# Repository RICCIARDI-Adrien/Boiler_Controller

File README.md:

# Boiler Controller

## Hardware
Schematics have been drawn using Eagle 8.3.1.  

### Power board
This board contains the AC/DC converter, the relays and the connector to the wall housing.

### Controller board
This board holds the microcontroller and the WiFi to UART bridge.

### Components
* [Single pole 16A relay with 5V coil](http://fr.farnell.com/oeg-te-connectivity/omih-ss-105lm-300/relais-spst-no-250vac-30vdc-16a/dp/1891727)
* [BD135 NPN bipolar transistor](http://fr.farnell.com/stmicroelectronics/bd135/transistor-npn-to-126/dp/9801529)
* [1N4007 rectifier diode](http://fr.farnell.com/multicomp/1n4007/diode-1a-1000v/dp/9565051)
* [15pF ceramic capacitor](http://fr.farnell.com/multicomp/mc0805n150j101a2-54mm/condensateur-mlcc-c0g-np0-15pf/dp/2112750)
* [100nF ceramic capacitor](http://fr.farnell.com/multicomp/mc0805b104k500a5-08mm/condensateur-mlcc-0-1uf-50v-x7r/dp/2395773)
* [10uF electrolytic capacitor](http://fr.farnell.com/multicomp/mcgpr16v106m5x11/condensateur-elec-alu-10uf-16v/dp/9451056)
* [10uF tantalum capacitor](http://fr.farnell.com/multicomp/mctar16v106kc/condensateur-tantale-10uf-16v/dp/2395815)
* [5V 2A AC/DC power supply](http://fr.farnell.com/vigortronix/vtx-214-010-205/alimentation-ac-dc-5v-2a/dp/2464685)
* [160ohm 1% resistor](http://fr.farnell.com/multicomp/mf12-160r/resistance-0-125w-1-160r/dp/9342672)
* [330ohm 5% resistor](http://fr.farnell.com/multicomp/mcf-0-25w-330r/resistance-couche-carbon-330r/dp/9339418)
* [470ohm 1% resistor](http://fr.farnell.com/multicomp/mf50-470r/resistance-0-5w-1-470r/dp/9340610)
* [1Kohm 5% resistor](http://fr.farnell.com/multicomp/mcf-0-25w-1k/resistance-couche-carbon-1k-0/dp/9339051)
* [1Kohm 1% resistor](http://fr.farnell.com/multicomp/mf50-1k/resistance-1k-0-5w-1/dp/9339779)
* [Fuseholder](http://fr.farnell.com/littelfuse/64900001039/porte-fusible-cms-20x5mm/dp/1271673)
* [Fuse](http://fr.farnell.com/littelfuse/0232002-mxp/fuse-cartridge-medium-acting-2a/dp/1707348)
* [2-pad terminal](http://fr.farnell.com/camdenboss/ctb0708-2/bornier-standard-2-voies-30-12awg/dp/2315273)
* [4-pad terminal](http://fr.farnell.com/camdenboss/ctb0708-4/bornier-standard-4-voies-30-12awg/dp/2315275)
* [Atmega328p microcontroller](http://fr.farnell.com/microchip/atmega328p-pu/micro-8-bits-avr-32k-flash-28pdip/dp/1715487)
* [3.6864MHz crystal](http://fr.farnell.com/iqd-frequency-products/lfxtal003263/quartz-3-686400mhz/dp/9712909)
* [3.3V LDO](http://fr.farnell.com/texas-instruments/lm1086ct-3-3-nopb/ic-reg-ldo-3-3v-1-5a-to-220/dp/1564628)
* [WiFi to UART bridge](https://www.gotronic.fr/art-module-wifi-uart-grove-113020010-23827.htm)
* [4-pin PCB male connector](https://www.gotronic.fr/art-connecteur-s004-5858.htm)
* [4-pin PCB female connector](https://www.gotronic.fr/art-connecteur-p004-5867.htm)
* [10-pin PCB male connector](https://www.gotronic.fr/art-connecteur-s010-15367.htm)
* [10-pin PCB female connector](https://www.gotronic.fr/art-connecteur-p010-15370.htm)

### Analog signals characteristics
* Day trimmer : resistance variation from 50 to 110ohm.
* Night trimmer : resistance variation from 0 to 60ohm.
* Radiator water start thermistor : resistance variation from 580 (+80°C) to 900ohm (-20°C).
* Outside thermistor : resistance variation from 340 (+40°C) to 480ohm (-10°C).
  
Microcontroller uses a 3.3V precision voltage reference for the ADC module to gain more precision with small variation signals. All voltage dividers must be calculated as the highest variable resistance value results in a 3.3V maximum voltage on the ADC pin.

### Fuse value calculation
AC/DC converter inrush current is 40A for less than 500us, so a temporized fuse is needed to allow the board to boot.  
AC/DC converter maximum input current is 150mA @ 240V, but due to enormous inrush current a big fuse must be used. A 250V/2A fuse has been chosen because this is the fuse used on the VTX-214 demo board (http://www.farnell.com/datasheets/1878969.pdf).

## Software

### Building microcontroller firmware
Install `avr-gcc` to build the microcontroller firmware.
  
Go to `Software/Microcontroller_Firmware` directory and type the following command to build the firmware :
```
make
```
File `Boiler_Controller_Firmware.elf` will be created.

### Flashing microcontroller firmware
You need to install `avrdude` to access to the programmer.  
Firmware can be burnt to the microcontroller memory by connecting an AVR ISP programmer to the controller board ISP connector and typing the command :
```
make flash
```
  
You can override the `PROGRAMMER_SERIAL_PORT` environment variable with the serial port your programmer is connected to.

### Building web server
You need to install `libmicrohttpd` library before building.  
On Debian/Ubuntu system, use the command `sudo apt install libmicrohttpd-dev`.  

To build the web server, go to `Software/Web_Server` directory and type `make`.

### Installing web server
Go to `Software/Web_Server` directory, build web server then type `sudo make install` to install server and init script.  
You can use `sudo make uninstall` command to uninstall the server and all related files.

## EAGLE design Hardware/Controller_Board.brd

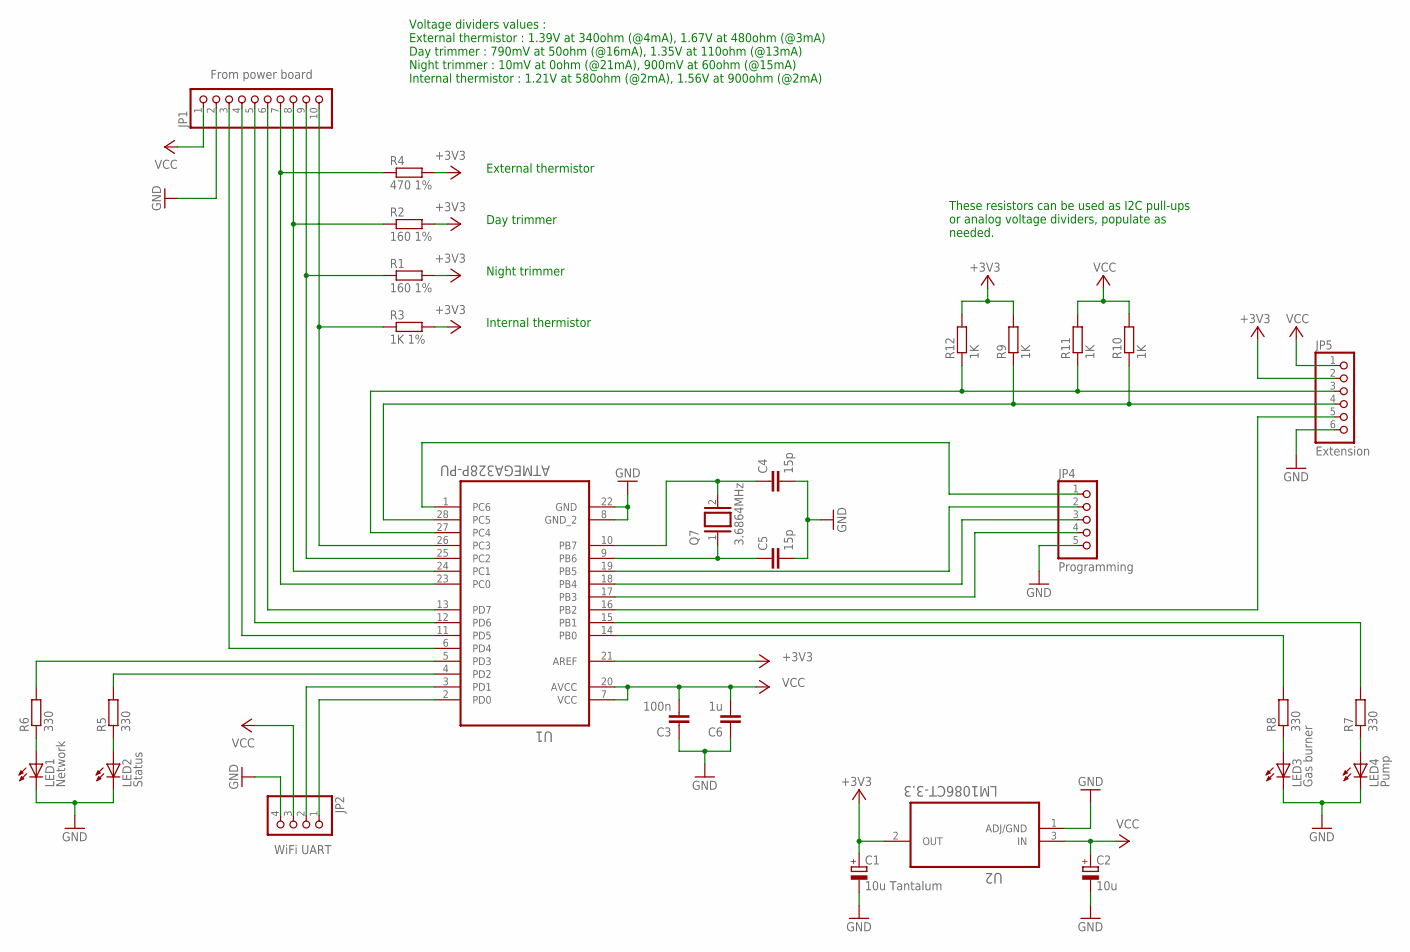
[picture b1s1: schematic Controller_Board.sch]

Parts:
C1: 10u Tantalum; E2,5-7
C2: 10u; E2,5-7
C3: 100n; C050-035X075
C4, C5: 15p; C025-050X050
C6: 1u; C050-035X075
JP1: From power board; 1X10
JP2: WiFi UART; 1X04
JP4: Programming; 1X05
JP5: Extension; 1X06
LED1: Network; LED5MM
LED2: Status; LED5MM
LED3: Gas burner; LED5MM
LED4: Pump; LED5MM
Q7: 3.6864MHz; QS
R1, R2: 160 1%; 0207/10
R3: 1K 1%; 0207/10
R4: 470 1%; 0207/10
R5, R6, R7, R8: 330; 0207/10
R9, R10, R11, R12: 1K; 0207/10
U1: ATMEGA328P-PU; DIP254P762X457-28
U2: LM1086CT-3.3; TO254P470X1016X2222-3P

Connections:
+3V3: C1.+, JP5.2, R1.2, R2.2, R3.2, R4.2, R9.2, R12.2, U1.21 (AREF), U2.2 (OUT)
GND: C1.-, C2.-, C3.1, C4.2, C5.2, C6.1, JP1.2, JP2.4, JP4.5, JP5.6, LED1.K (C), LED2.K (C), LED3.K (C), LED4.K (C), U1.8 (GND_2), U1.22 (GND), U2.1 (ADJ/GND)
unnamed: JP1.10, R3.1, U1.26 (PC3)
unnamed: JP1.9, R1.1, U1.25 (PC2)
unnamed: JP1.8, R2.1, U1.24 (PC1)
unnamed: JP1.7, R4.1, U1.23 (PC0)
unnamed: JP1.6, U1.13 (PD7)
unnamed: JP1.5, U1.12 (PD6)
unnamed: JP1.4, U1.11 (PD5)
unnamed: JP1.3, U1.6 (PD4)
unnamed: JP2.2, U1.3 (PD1)
unnamed: JP2.1, U1.2 (PD0)
unnamed: LED1.A, R6.1
unnamed: LED2.A, R5.1
unnamed: R6.2, U1.5 (PD3)
unnamed: R5.2, U1.4 (PD2)
unnamed: JP4.2, U1.19 (PB5)
unnamed: JP4.3, U1.18 (PB4)
unnamed: JP4.4, U1.17 (PB3)
unnamed: JP4.1, U1.1 (PC6)
unnamed: JP5.3, R11.1, R12.1, U1.27 (PC4)
unnamed: LED4.A, R7.1
unnamed: LED3.A, R8.1
unnamed: JP5.4, R9.1, R10.1, U1.28 (PC5)
unnamed: R8.2, U1.14 (PB0)
unnamed: R7.2, U1.15 (PB1)
unnamed: JP5.5, U1.16 (PB2)
unnamed: C4.1, Q7.2, U1.10 (PB7)
unnamed: C5.1, Q7.1, U1.9 (PB6)
VCC: C2.+, C3.2, C6.2, JP1.1, JP2.3, JP5.1, R10.2, R11.2, U1.7 (VCC), U1.20 (AVCC), U2.3 (IN)

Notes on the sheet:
Night trimmer
Day trimmer
Internal thermistor
External thermistor
Voltage dividers values : External thermistor : 1.39V at 340ohm (@4mA), 1.67V at 480ohm (@3mA) Day trimmer : 790mV at 50ohm (@16mA), 1.35V at 110ohm (@13mA) Night trimmer : 10mV at 0ohm (@21mA), 900mV at 60ohm (@15mA) Internal thermistor : 1.21V at 580ohm (@2mA), 1.56V at 900ohm (@2mA)
These resistors can be used as I2C pull-ups or analog voltage dividers, populate as needed.

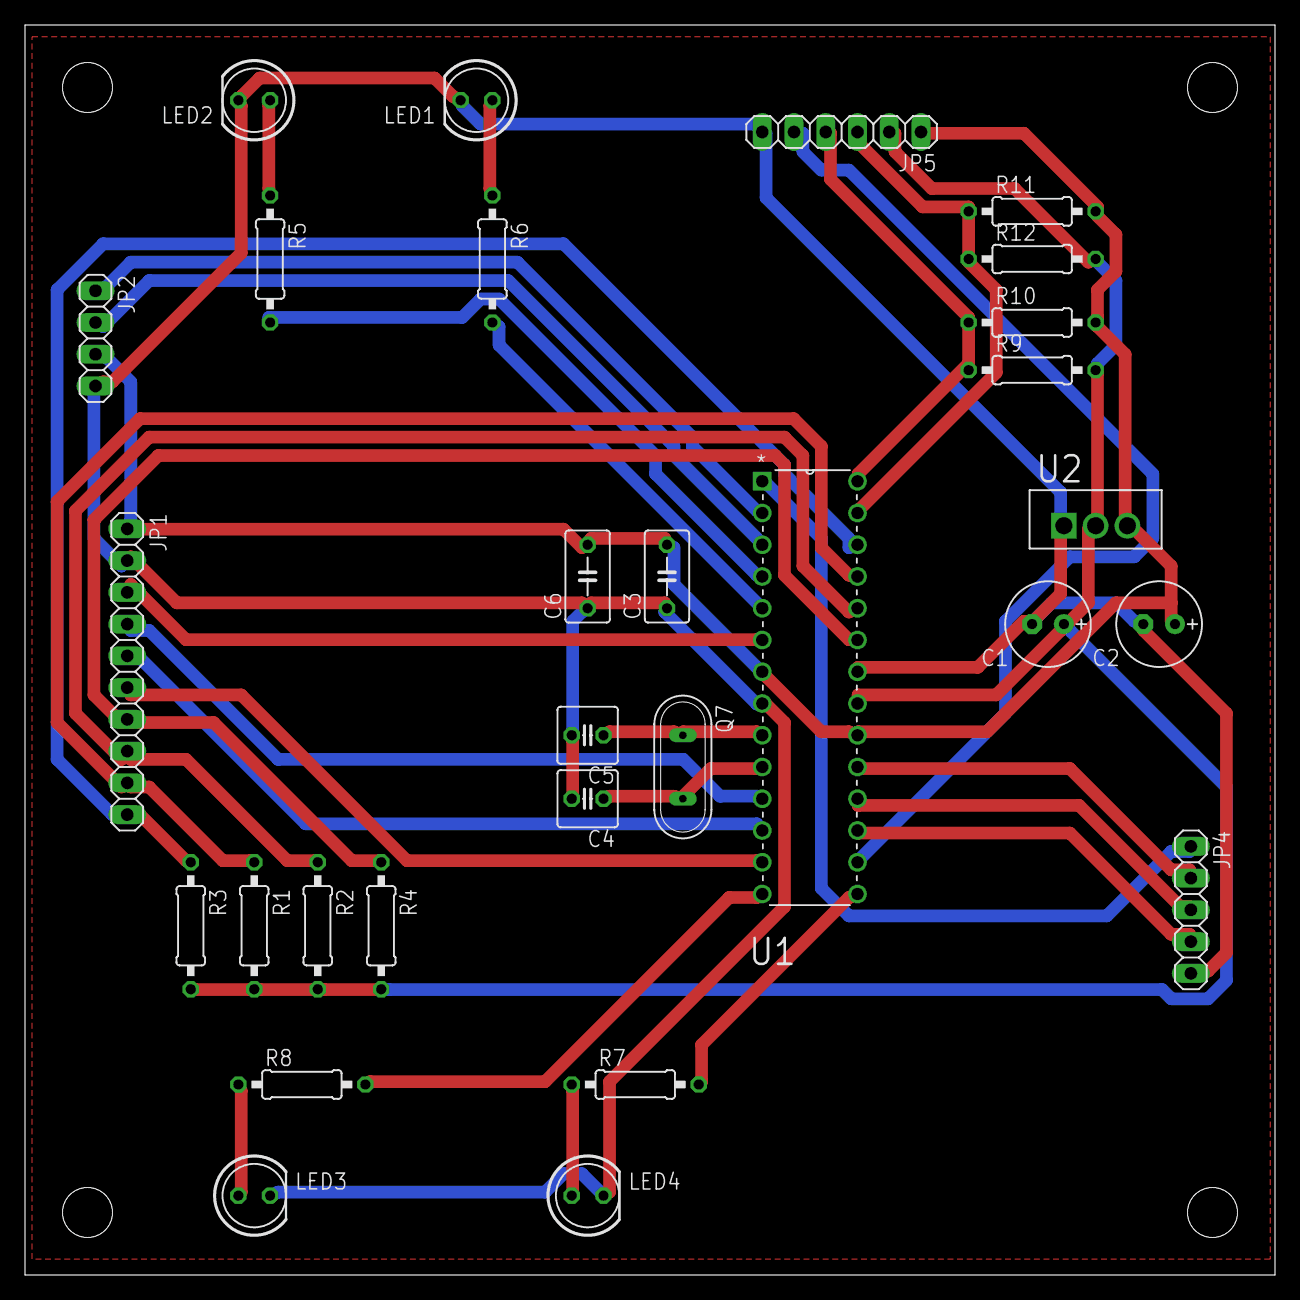
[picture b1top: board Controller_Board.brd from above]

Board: 2 copper layers, 100.0 x 100.0 mm, 29 parts (0 on the bottom side), 30 nets.

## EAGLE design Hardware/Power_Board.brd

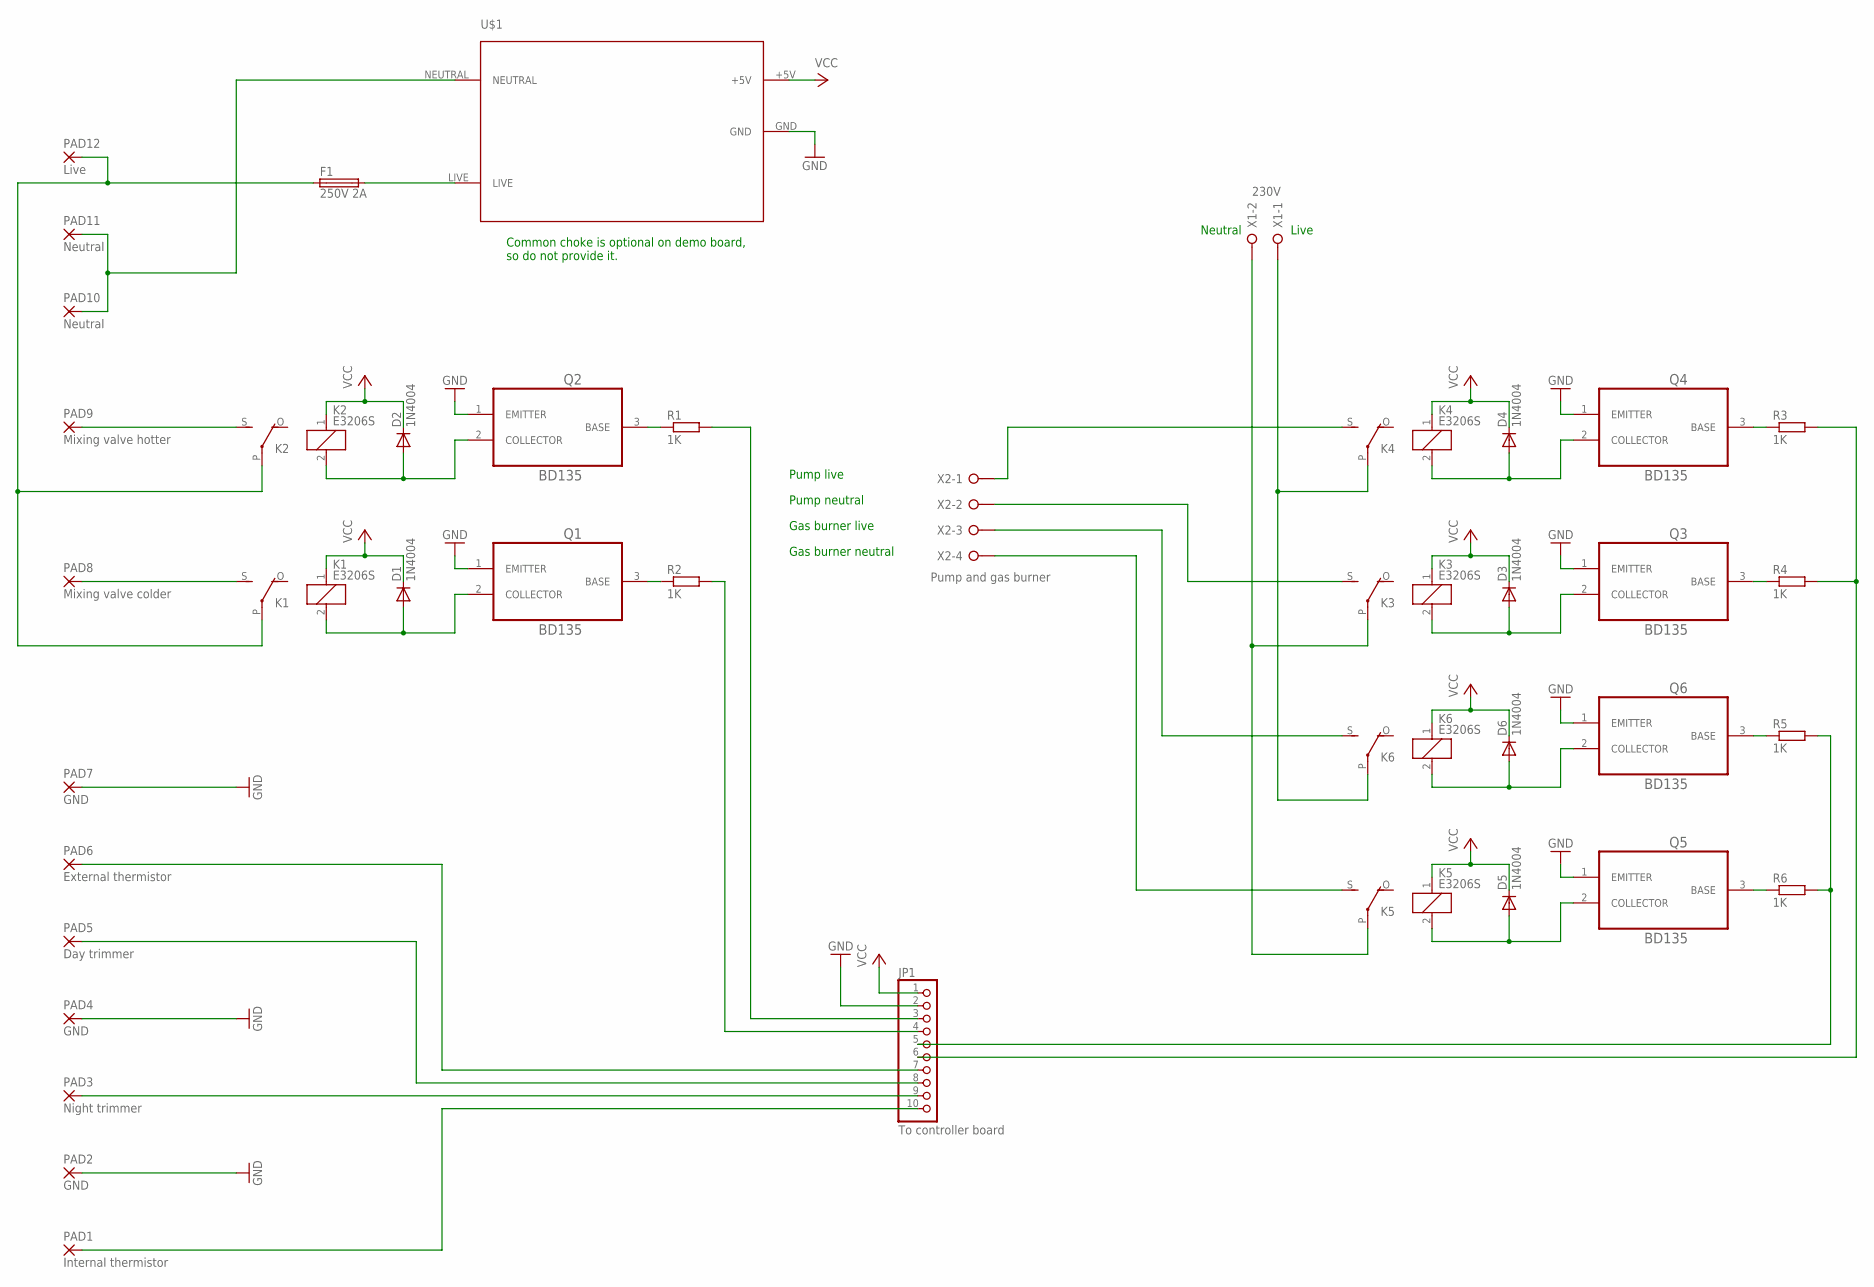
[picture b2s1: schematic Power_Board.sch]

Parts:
D1, D2, D3, D4, D5, D6: 1N4004; DO41-10
F1: 250V 2A; GSH15
JP1: To controller board; 1X10
K1, K2, K3, K4, K5, K6: E3206S
PAD1: Internal thermistor; SMD2,54-20,32
PAD2, PAD4, PAD7: GND; SMD2,54-20,32
PAD3: Night trimmer; SMD2,54-20,32
PAD5: Day trimmer; SMD2,54-20,32
PAD6: External thermistor; SMD2,54-20,32
PAD8: Mixing valve colder; SMD2,54-20,32
PAD9: Mixing valve hotter; SMD2,54-20,32
PAD10, PAD11: Neutral; SMD2,54-20,32
PAD12: Live; SMD2,54-20,32
Q1, Q2, Q3, Q4, Q5, Q6: BD135; TRANS_BD135
R1, R2, R3, R4, R5, R6: 1K; 0207/10
U$1: VTX-214-010-205
X1: 230V; W237-132
X2: Pump and gas burner; W237-4P

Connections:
GND: JP1.2, PAD2.1, PAD4.1, PAD7.1, Q1.1 (EMITTER), Q2.1 (EMITTER), Q3.1 (EMITTER), Q4.1 (EMITTER), Q5.1 (EMITTER), Q6.1 (EMITTER), U$1.GND
unnamed: JP1.8, PAD5.1
unnamed: JP1.10, PAD1.1
unnamed: K1.S, PAD8.1
unnamed: D1.A, K1.2, Q1.2 (COLLECTOR)
unnamed: Q2.3 (BASE), R1.1
unnamed: K2.S, PAD9.1
unnamed: D2.A, K2.2, Q2.2 (COLLECTOR)
unnamed: JP1.7, PAD6.1
unnamed: JP1.4, R2.2
unnamed: F1.1, K1.P, K2.P, PAD12.1
unnamed: K5.S, X2.4
unnamed: K3.S, X2.2
unnamed: D3.A, K3.2, Q3.2 (COLLECTOR)
unnamed: K4.S, X2.1
unnamed: D4.A, K4.2, Q4.2 (COLLECTOR)
unnamed: Q1.3 (BASE), R2.1
unnamed: D5.A, K5.2, Q5.2 (COLLECTOR)
unnamed: K6.S, X2.3
unnamed: D6.A, K6.2, Q6.2 (COLLECTOR)
unnamed: Q5.3 (BASE), R6.1
unnamed: Q6.3 (BASE), R5.1
unnamed: Q3.3 (BASE), R4.1
unnamed: JP1.5, R5.2, R6.2
unnamed: Q4.3 (BASE), R3.1
unnamed: K4.P, K6.P, X1.1
unnamed: JP1.6, R3.2, R4.2
unnamed: PAD10.1, PAD11.1, U$1.NEUTRAL
unnamed: K3.P, K5.P, X1.2
unnamed: F1.2, U$1.LIVE
unnamed: JP1.3, R1.2
PIN4: JP1.9, PAD3.1
VCC: D1.C, D2.C, D3.C, D4.C, D5.C, D6.C, JP1.1, K1.1, K2.1, K3.1, K4.1, K5.1, K6.1, U$1.+5V

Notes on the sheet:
Pump live
Pump neutral
Gas burner live
Gas burner neutral
Live
Neutral
Common choke is optional on demo board, so do not provide it.

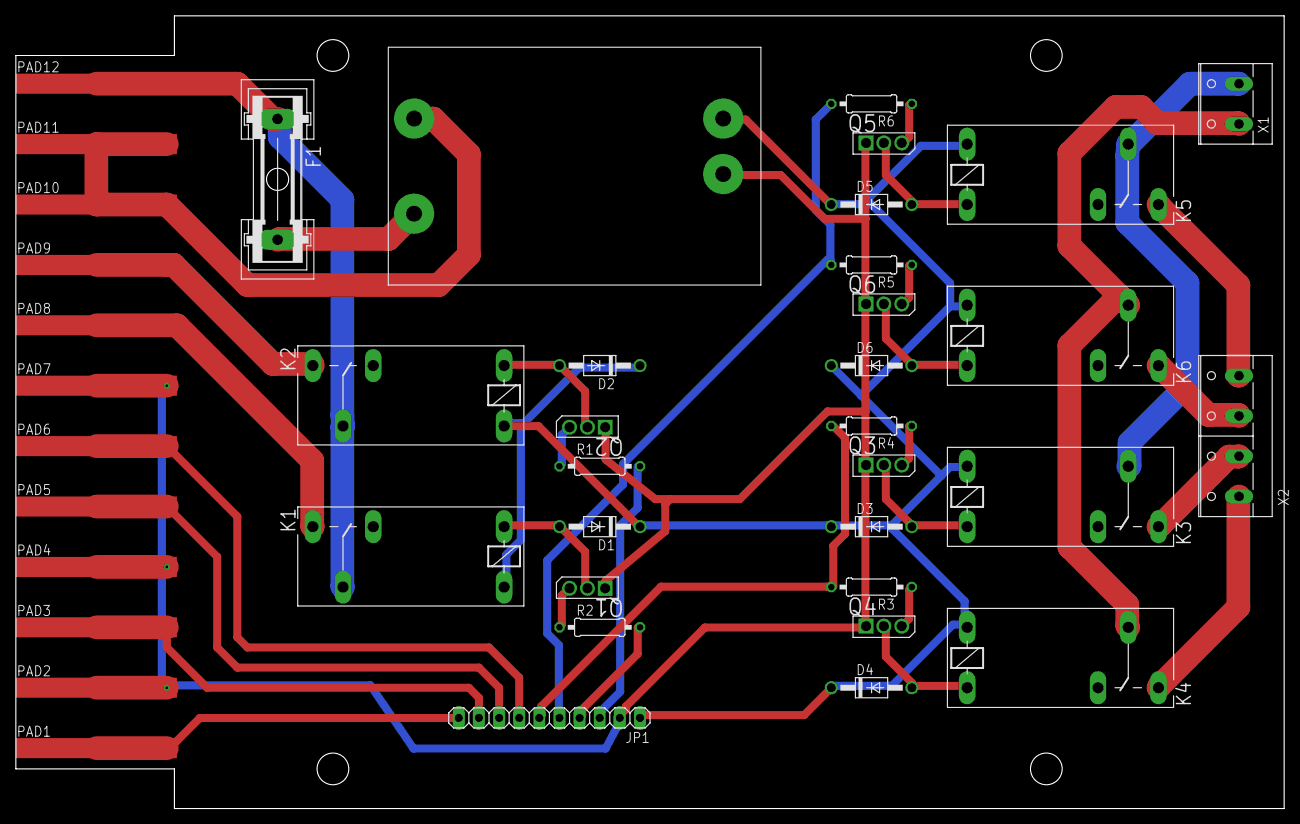
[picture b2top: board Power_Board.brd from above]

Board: 2 copper layers, 160.0 x 100.0 mm, 41 parts (0 on the bottom side), 33 nets.

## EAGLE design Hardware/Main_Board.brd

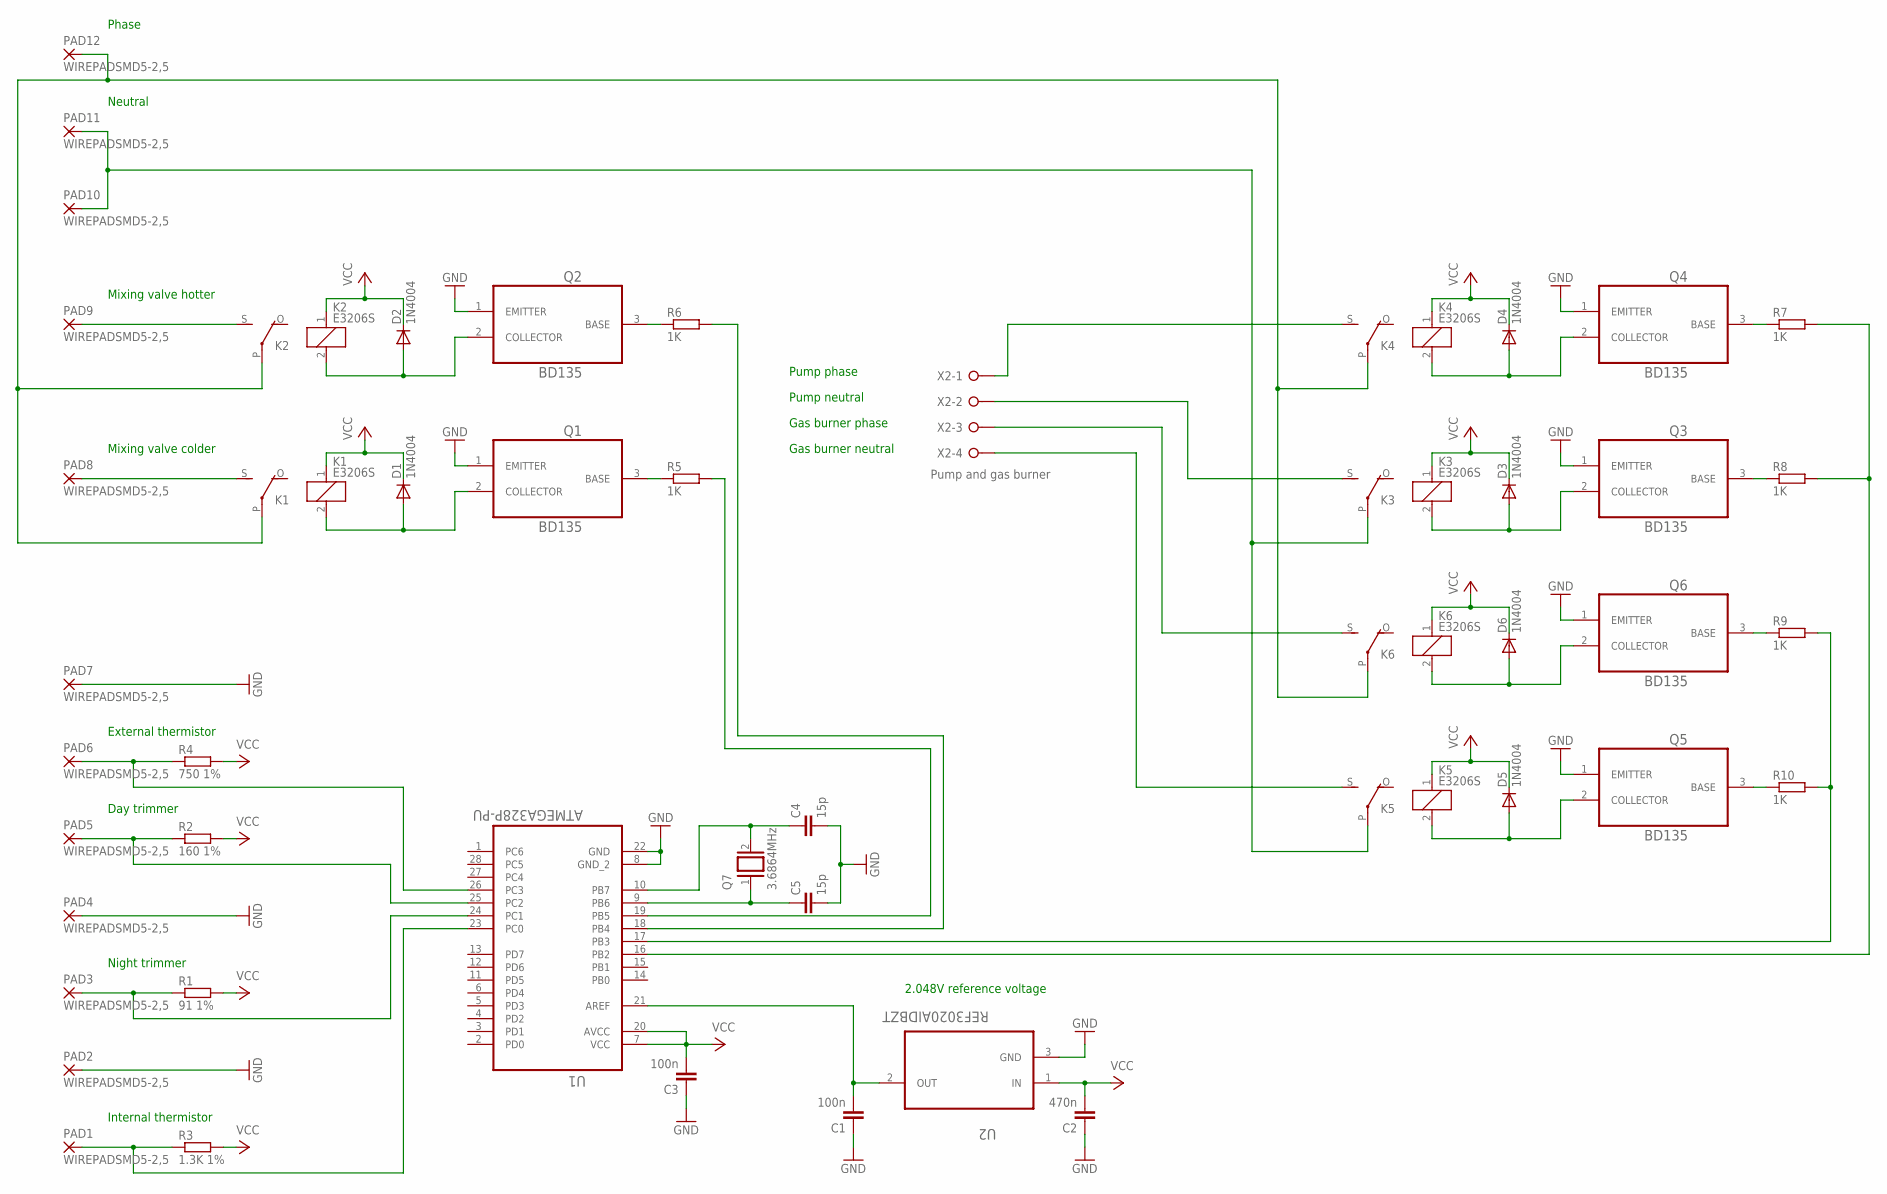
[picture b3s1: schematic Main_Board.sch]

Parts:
C1, C3: 100n; C050-035X075
C2: 470n; C050-035X075
C4, C5: 15p; C025-030X050
D1, D2, D3, D4, D5, D6: 1N4004; DO41-10
K1, K2, K3, K4, K5, K6: E3206S
PAD1, PAD2, PAD3, PAD4, PAD5, PAD6, PAD7, PAD8, PAD9, PAD10, PAD11, PAD12: WIREPADSMD5-2,5; 5-2,5
Q1, Q2, Q3, Q4, Q5, Q6: BD135; TRANS_BD135
Q7: 3.6864MHz; QS
R1: 91 1%; 0207/10
R2: 160 1%; 0207/10
R3: 1.3K 1%; 0207/10
R4: 750 1%; 0207/10
R5, R6, R7, R8, R9, R10: 1K; 0207/10
U1: ATMEGA328P-PU; DIP254P762X457-28
U2: REF3020AIDBZT; SOT95P237X112-3N
X2: Pump and gas burner; W237-4P

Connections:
GND: C1.1, C2.1, C3.1, C4.2, C5.2, PAD2.1, PAD4.1, PAD7.1, Q1.1 (EMITTER), Q2.1 (EMITTER), Q3.1 (EMITTER), Q4.1 (EMITTER), Q5.1 (EMITTER), Q6.1 (EMITTER), U1.8 (GND_2), U1.22 (GND), U2.3 (GND)
unnamed: PAD5.1, R2.1, U1.25 (PC2)
unnamed: PAD1.1, R3.1, U1.23 (PC0)
unnamed: K1.S, PAD8.1
unnamed: D1.A, K1.2, Q1.2 (COLLECTOR)
unnamed: Q4.3 (BASE), R7.1
unnamed: K2.S, PAD9.1
unnamed: D2.A, K2.2, Q2.2 (COLLECTOR)
unnamed: PAD6.1, R4.1, U1.26 (PC3)
unnamed: Q1.3 (BASE), R5.1
unnamed: K1.P, K2.P, K4.P, K6.P, PAD12.1
unnamed: K5.S, X2.4
unnamed: K3.S, X2.2
unnamed: D3.A, K3.2, Q3.2 (COLLECTOR)
unnamed: K4.S, X2.1
unnamed: D4.A, K4.2, Q4.2 (COLLECTOR)
unnamed: C1.2, U1.21 (AREF), U2.2 (OUT)
unnamed: D5.A, K5.2, Q5.2 (COLLECTOR)
unnamed: K6.S, X2.3
unnamed: D6.A, K6.2, Q6.2 (COLLECTOR)
unnamed: Q2.3 (BASE), R6.1
unnamed: R5.2, U1.19 (PB5)
unnamed: R6.2, U1.18 (PB4)
unnamed: R9.2, R10.2, U1.17 (PB3)
unnamed: Q5.3 (BASE), R10.1
unnamed: Q6.3 (BASE), R9.1
unnamed: R7.2, R8.2, U1.16 (PB2)
unnamed: C4.1, Q7.2, U1.10 (PB7)
unnamed: Q3.3 (BASE), R8.1
unnamed: C5.1, Q7.1, U1.9 (PB6)
unnamed: K3.P, K5.P, PAD10.1, PAD11.1
PIN4: PAD3.1, R1.1, U1.24 (PC1)
VCC: C2.2, C3.2, D1.C, D2.C, D3.C, D4.C, D5.C, D6.C, K1.1, K2.1, K3.1, K4.1, K5.1, K6.1, R1.2, R2.2, R3.2, R4.2, U1.7 (VCC), U1.20 (AVCC), U2.1 (IN)

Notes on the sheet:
Night trimmer
Day trimmer
Internal thermistor
External thermistor
Mixing valve colder
Mixing valve hotter
Pump phase
Pump neutral
Gas burner phase
Gas burner neutral
Phase
Neutral
2.048V reference voltage

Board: 2 copper layers, 49 parts (0 on the bottom side), 33 nets, no tracks yet.

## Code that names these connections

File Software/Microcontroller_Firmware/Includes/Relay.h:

/** @file Relay.h
 * Simple wrapper to easily control the board relays.
 * @author Adrien RICCIARDI
 */
#ifndef H_RELAY_H
#define H_RELAY_H

//-------------------------------------------------------------------------------------------------
// Types
//-------------------------------------------------------------------------------------------------
/** All available relays. */
typedef enum
{
	RELAY_ID_MIXING_VALVE_LEFT = 4, //!< Connected to PD4 pin.
	RELAY_ID_MIXING_VALVE_RIGHT = 5, //!< Connected to PD5 pin.
	RELAY_ID_PUMP = 6, //!< Connected to PD6 pin.
	RELAY_ID_GAS_BURNER = 7 //!< Connected to PD7 pin.
} TRelayID;

//-------------------------------------------------------------------------------------------------
// Functions
//-------------------------------------------------------------------------------------------------
/** Configure the needed GPIOs to access relays. */
void RelayInitialize(void);

/** Close a relay circuit.
 * @param Relay_ID The relay to close.
 */
void RelayTurnOn(TRelayID Relay_ID);

/** Open a relay circuit.
 * @param Relay_ID The relay to open.
 */
void RelayTurnOff(TRelayID Relay_ID);

#endif

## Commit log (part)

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2017-07-05 Initial commit. Added schematics analog sampling part.
2017-07-05 Renamed schematics file for more coherency.
2017-07-05 Used more generic resistors in the voltage dividers.
2017-07-05 Added more components to the README list.
2017-07-05 Added BD135 transistor Eagle library.
2017-07-06 Added relay blocks to the schematics.
2017-07-08 Used an ATMEGA328 microcontroller to sample analog signals and to control the relays.
2017-07-08 Replaced +5V supply signal by Vcc for more coherency.
2017-07-08 Fixed reference voltage input pin capacitor value.
2017-07-10 Splitted circuit in two PCBs to ease routing.
2017-07-10 Decreased a bit the controller board schematics height.
2017-07-14 Updated components list.
2017-07-29 Started microcontroller firmware implementation. Made a blinking led test.
2017-08-06 Started microcontroller protocol module implementation. Non-interrupt UART driver part is working.
2017-08-06 Configured ESP8266 UART to WiFi module to act as a transparent brigde.
2017-08-24 Added protocol reception and transmission state machines to microcontroller firmware, also implemented 'get firmware version' command.
2017-08-24 Started test server implementation. Server can send commands and retrieve answers.
2017-08-24 Added ADC driver and sampling task to microcontroller firmware.
2017-08-24 Added 'get temperatures' command to microcontroller firmware.
2017-08-24 Added 'get temperature' command test to the test server.
2017-08-25 Made AC/DC converter Eagle component library.
2017-09-02 Increased AC/DC package pads diameter and drill diameter to make sure the component will fit.
2017-09-10 Added a 2-pad terminal to supply the pump and the gas burner from a different 230V source than the one provided by the wall housing, which might not be powerful enough.
2017-09-11 Added power board PCB.
2017-11-01 Added a fuse to the power board and made PCB routes thicker.
2017-11-01 Updated power board schematic and PCB images.
2017-11-01 Added holes to the power board PCB to attach the controller board PCB to.
2017-11-02 Added bigger pads to the power board PCB, so the PCB coating won't recover the pads.
2017-11-19 Removed old main board file (useless now because the initial board has been splitted in two separate boards.
2017-11-19 Added one more decoupling capacitor close to the control board microcontroller, changed 15pF capacitors package to the good one, added a second led just in case.
2017-11-20 Added spare leds and connector to the controller board. Components could be populated if needed.
2017-11-20 Added controller board PCB.
2017-11-25 Added a little delay between ESP8266 connection and first command sending to the server test script to make it work even on ESP8266 initial boot.
2017-11-25 Added relays support to microcontroller firmware.
2017-11-25 Automatically reset the ESP8266 module on microcontroller boot to avoid powering off then powering on the whole board after programming the microcontroller.
2017-12-03 Started bootloader implementation. For now bootloader makes a led blink then jumps to application area.
2017-12-03 Added UART module to microcontroller bootloader.
2017-12-03 Increased bootloader space to maximum value, disabled standard libraries to keep some space.
2017-12-03 Configured maximum oscillator startup time to ensure it is stable when UART is used.
2017-12-03 Added fuses flashing from firmware (this will be removed when bootloader will be working).
2017-12-03 Added WiFi connection failure detection to firmware.
2017-12-03 Enabled size optimization for firmware to remove delay functions compilation warning. This decreased code size by 4.
2017-12-03 Added a led module to the firmware to easily handle the multiple controller board leds.
2017-12-05 Updated README.md components list.
2017-12-05 Updated controller board PCB with new LDO reference voltage.
2017-12-15 Added a ground plane to the controller board to increase the copper plating index.
2017-12-16 Added +3.3V and a GPIO to the controller board extension connector.
2017-12-17 Made sure all relays are turned off on microcontroller initialization sequence.
2017-12-17 Added external and start thermistors temperature conversion utility and the related protocol commands.
2017-12-17 Added Celsius converted temperatures retrieving test to test server.
2017-12-17 Gave more coherent names to thermistors and temperatures in the microcontroller firmware.
2017-12-17 Added mixing valve control module to microcontroller firmware.
2017-12-17 Added 'get mixing valve position' command to microcontroller firmware communication protocol.
2017-12-17 Cleaned microcontroller firmware initialization sequence, started control loop implementation.
2018-01-02 Added 'set mixing valve maximum moving time' command to microcontroller firmware.
2018-01-07 Made a difference between sensor temperatures and other temperatures (like trimmers ones or the room desired temperature) for more coherency.
2018-01-07 Added day and night trimmers temperature retrieval functions.
2018-01-07 Added a function to determine currently desired room temperature according to trimmers position, time of the day and protocol ability to set desired temperature.
2018-01-07 Added a protocol command to switch between night and day modes.
2018-01-07 Added a protocol command to set the desired room temperature.
2018-01-07 Added heating curve computation.
2018-01-07 Added gas burner control to microcontroller firmware.
2018-01-07 Made cached temperature variables local in microcontroller firmware main() function because these variables are not shared with Main module private functions.
2018-01-11 Updated microcontroller firmware led module to final hardware.
2018-01-14 Added 'get trimmers raw values' protocol command.
2018-01-14 Set real mixing valve maximum moving time.
2018-01-14 Added return temperature ADC channel (PC4 pin).
2018-01-14 Added 'set boiler running mode' protocol command.
2018-01-14 Taken into account boiler 'running' and 'idle' states. Adapted mixing valve behavior to these new states.
2018-01-14 Removed now useless 'set mixing valve maximum moving time' protocol command.
2018-01-14 Updated README.md with information about firmware building and flashing, removed bootloader section and updated ADC reference voltage value.
2018-01-14 Removed useless microcontroller bootloader.
2018-01-14 Moved 'is night mode' feature to Protocol module for more coherency.
2018-01-28 Made night trimmer use day trimmer as base value in microcontroller firmware.
2018-01-28 Added a microcontroller firmware command to get the desired room temperature.
2018-02-03 Removed unused 'radiator return temperature' value from microcontroller firmware 'get sensors Celsius temperatures' protocol command.
2018-02-03 Added server library initial version.
2018-02-03 Modified tests server to use server library.
2018-02-04 Added a moving average computation on each sampled ADC channel to filter signal spikes.
2018-02-04 Added separated high and low values for the gas burner hysteresis.
2018-02-04 Fixed protocol command payload reception in microcontroller firmware.
2018-02-04 Fixed a bad variable name in the server library.
2018-02-04 Fixed a bad variable name and added a delay in the tests server.
2018-02-04 Made sure gas burner is stopped when boiler running mode is set to off.
2018-02-04 Directly used CONFIGURATION_MIXING_VALVE_MAXIMUM_MOVING_TIME constant in microcontroller firmware Mixing_Valve module because this value is no more configurable through a protocol command.
2018-02-04 Added 'avrdude' to the README.md list of programs to install.
2018-02-04 Removed useless shebang in server library.
2018-02-04 Moved microcontroller firmware target start water temperature computation to a dedicated task to allow to report the value thanks to a protocol command.
2018-02-04 Added a microcontroller firmware protocol command to retrieve target start water temperature value.
2018-02-04 Optimized some microcontroller firmware MixingValveSetPosition() function code.
2018-02-04 Added getTargetStartWaterTemperature() function to server library.
2018-02-04 Displayed target start water temperature in tests server.
2018-02-04 Added server library functions documentation.
2018-02-13 Added 'get heating curve parameters' command to microcontroller firmware.
2018-02-13 Added 'set heating curve parameters' command to microcontroller firmware.
2018-02-13 Added 'get heating curve parameters' command to server library.
2018-04-16 Fixed a bug in the microcontroller 'set heating curve parameters' protocol command (expected payload was not defined).
2018-04-16 Added 'set heating curve parameters' command to server library.
2018-04-17 Replaced all dirty byte shifts in server library by cleaner 'struct' module.
2018-04-17 Displayed heating curve parameters in test server.
2018-04-17 Added a python script to configure heating curve parameters.
2019-02-09 Started web server implementation.
2019-02-09 Added web server 'index' page creation. Form values are not handled yet.
2019-02-09 Started boiler board TCP server implementation in web server.
2019-02-09 Improved microcontroller firmware 'get desired room temperature' and 'set desired room temperature' to be able to get and set night and day temperatures separately.
2019-02-09 Added desired day and night temperatures reading from board to web server and displayed the values in the corresponding HTML page.
2019-02-09 Added 'get boiler running mode' communication protocol command to microcontroller firmware.
2019-02-09 Added HTML page arguments value retrieval to web server 'index' page handler.
2019-02-09 Set power mode and desired temperatures according to HTML data in web server 'index' page handler.
2019-02-12 Added installation and uninstallation makefile rules.
2019-02-12 Allowed to change mixing valve position even if it has not finished previous move.
2019-02-12 Added final server IP address to microcontroller firmware configuration to avoid setting it each time.
2019-02-12 Fixed memory leaks in web server 'index' page arguments parsing; fixed sending uninitialized argument values to board.
2019-02-12 Removed useless fix that tried to free a static string in the web server.
2019-02-15 Improved firmware main loop by executing running and idle actions only when boiler running state changes.
2019-02-15 Used remaining led to indicate whether mixing valve is moving.
2019-11-08 Updated README.md with server building and installing information.
2019-11-08 Added internal EEPROM write function to microcontroller firmware.
2019-11-08 Added heating curve parameters loading from and storing to internal EEPROM to microcontroller firmware.
2019-11-08 Moved web server index page generation to a dedicated file.
2019-11-08 Displayed starting and outside temperatures to web server index page.
2019-11-08 Added automatic refresh to web server index page.
2019-11-08 Improved target radiator start water temperature displayed text on web server index page.
2019-11-08 Added heating curve parameters displaying to web server index page.
2019-11-08 Increased web server index page automatic refreshing to 10 seconds.
2020-10-04 Improved web server systemd unit dependency to make the unit start at the right moment.
2020-10-04 Consider boiler as stopped on firmware boot.
2020-10-04 Enabled keep alive on TCP connection between board and server to avoid board disconnecting and reconnecting when server is not active.
2020-10-04 Added web server settings page user interface (no logic for now).
2020-10-04 Lighted idle led at firmware boot to tell that boiler is idle.
2020-10-04 Prevented user from setting an empty heating curve in web server settings page.
2020-10-04 Added 'set heating curve parameters' command to web server.
2020-10-04 Added heating curve parameters setting logic to web server settings page.
2020-10-04 Added empty monitoring web server page.
2020-10-04 Added web server monitoring page logic.
2020-10-04 Linked monitoring page to index page in web server.
2020-10-04 Fixed a bug in BoilerGetTargetRadiatorStartWaterTemperature() return value.
2020-10-04 Forced boiler in running mode at microcontroller boot.
